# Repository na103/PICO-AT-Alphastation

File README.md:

# PICO-AT Power Adapter for DEC Alphastation 200
This adapter allows you to replace the original  DEC Alphastation 200 PSU  with a newer ATX PSU.<br>

## Bill of materials
| Qt. |    Description     |             Designator          |    Mouser  Part    |   
|:---:|--------------------|---------------------------------|--------------------|
|1    |Capacitor 2.2uF     | C1                              |T491C225K035AT      |
|1    |Capacitor 1uF       | C2                              |T491C105K050AT      |
|1    |SMD LED             | D4                              |150080VS75000       |
|1    |ATX 24pin fem conn  | J1                              |87427-2402          |
|1    |Resistor 330R       | R4                              |CR0805-FX-3300ELF   |
|1    |Regulator L7905     | U1                              |L7905CV             |
<br>

## Building notes
The adapter is designed to use the old power cables, power switch and external fan. You must  desolder them from the old one, being careful not to break the terminals.<br>

the original psu provides power and control for external 12V fan on the chassis via a temperature sensor<br>
The adapter does not include temperature sensor control, so the fan will always be active.
<br>
Due to the limited space inside the case you need to find a location for the adapter to ensure proper insulation.<br>
maybe if you shortened the cables you could place it inside the ATX PSU

## Note for ATX PSU replacement
The original ASTEC model AA 19100 power supply has the following characteristics, buy an ATX PSU capable of delivering this power.<br>

| DC output voltage | Current (max) | Cable colour |
|-------------------|---------------|--------------|
| +3.3V             | 35A           | Orange       |
| +12V              | 4.6A          | Blue         |
| +5V               | 30A           | Red          |
| -5V               | 0.3A          | Gray         |
| -12V              | 0.3A          | Yellow       |

<br>

## Thanks

Thankyou to all the people who have helped with this project.

- [Wiretrap-retro](https://github.com/wiretap-retro) who created the [PICO-AT](https://github.com/wiretap-retro/PICO-AT-Power-Adapter) that I used as the base design project
- |D|A|V| for testing the adapter in your DEC Alphastation 200

<br>
If you found this my work useful, please consider buying me a cup of coffee if you want:<br>

## License

This work is licensed under a Creative Commons Attribution 4.0 International License. See [https://creativecommons.org/licenses/by/4.0/](https://creativecommons.org/licenses/by/4.0/).

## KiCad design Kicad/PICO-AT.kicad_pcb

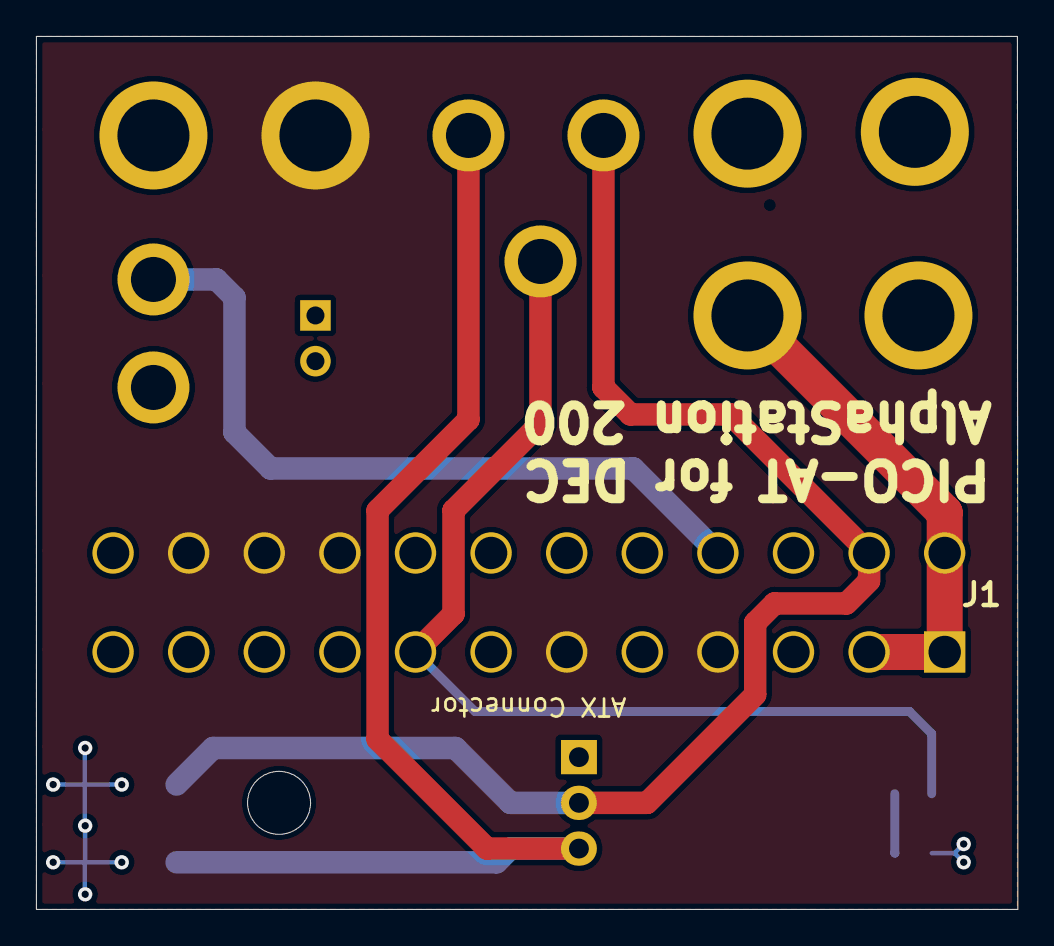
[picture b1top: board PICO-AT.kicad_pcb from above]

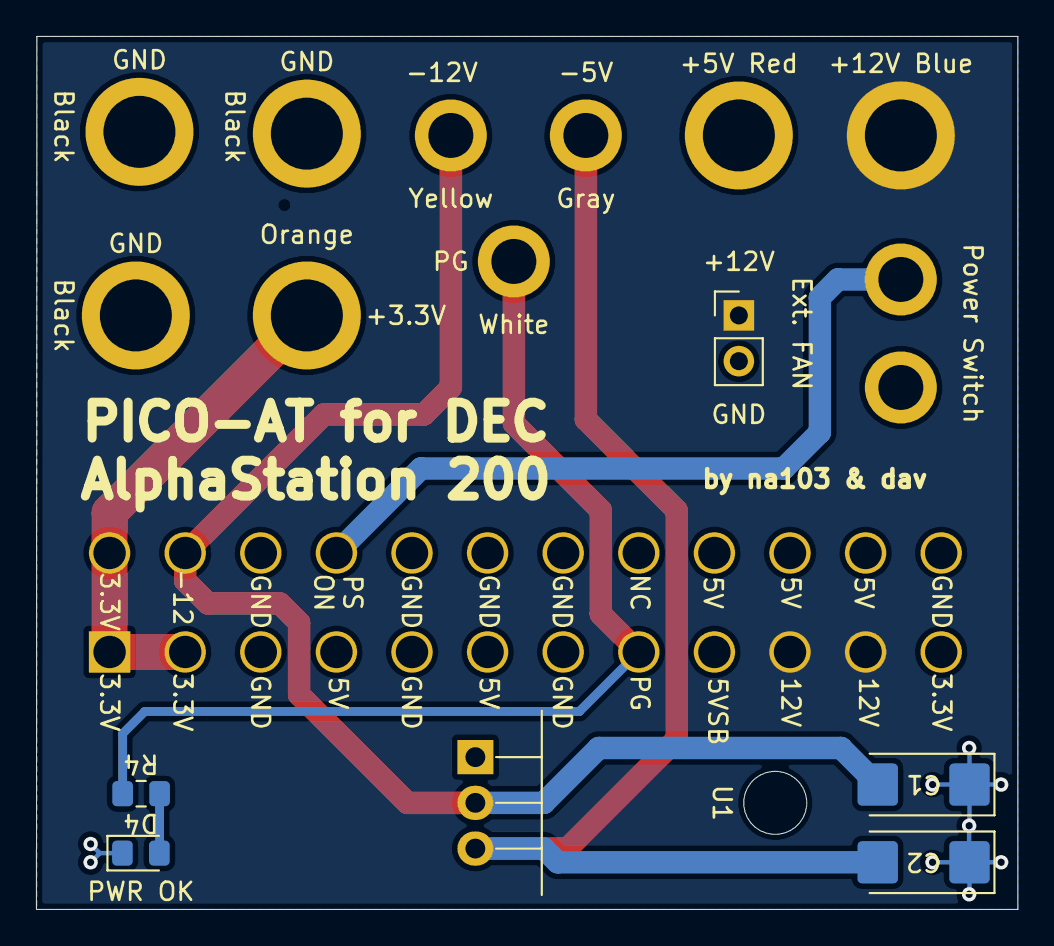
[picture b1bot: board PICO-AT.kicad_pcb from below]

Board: 4 copper layers, 54.5 x 48.5 mm, 17 parts (6 on the bottom side), 9 nets.

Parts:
+3.3V: Orange; PowerSupply_1x01_P4mm
+5V Red: 5V; PowerSupply_1x01_P4mm
+12V: Ext. FAN; PinHeader_1x02_P2.54mm_Vertical
+12V Blue: 12V; PowerSupply_1x01_P4mm
-5V: Gray; PowerSupply_1x01_P2.5mm
-12V: Yellow; PowerSupply_1x01_P2.5mm
C1: 2.2uF; CP_EIA-6032-28_Kemet-C_Pad2.25x2.35mm_HandSolder
C2: 1uF; CP_EIA-6032-28_Kemet-C_Pad2.25x2.35mm_HandSolder
D4: PWR OK; LED_0805_2012Metric_Pad1.15x1.40mm_HandSolder
GND: Power Switch; PowerSupply_1x02_P2.5mm
GND#2, GND#3, GND#4: Black; PowerSupply_1x01_P4mm
J1: 87427-2402; 87427-24YY_347202
PG: White; PowerSupply_1x01_P2.5mm
R4: 330; R_0805_2012Metric_Pad1.15x1.40mm_HandSolder
U1: L7905; TO-220-3_Horizontal_TabDown

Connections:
/3.3V: +3.3V.1, J1.1, J1.2, J1.13
/5V: +5V Red.1, J1.4, J1.6, J1.21, J1.22, J1.23
/12V: +12V.1, +12V Blue.1, J1.10, J1.11
/-5V: -5V.1, C2.2, U1.3
/-12V: -12V.1, C1.2, J1.14, U1.2
/GND: +12V.2, C1.1, C2.1, D4.1, GND.2, GND#2.1, GND#3.1, GND#4.1, J1.3, J1.5, J1.7, J1.15, J1.17, J1.18, J1.19, J1.24, U1.1
/PG: J1.8, PG.1, R4.1
/PS-ON: GND.1, J1.16
unnamed: D4.2, R4.2

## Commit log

2023-10-26 PSU ASTEC
2023-10-26 license
2023-10-26 kicad project
2023-10-26 pictures
